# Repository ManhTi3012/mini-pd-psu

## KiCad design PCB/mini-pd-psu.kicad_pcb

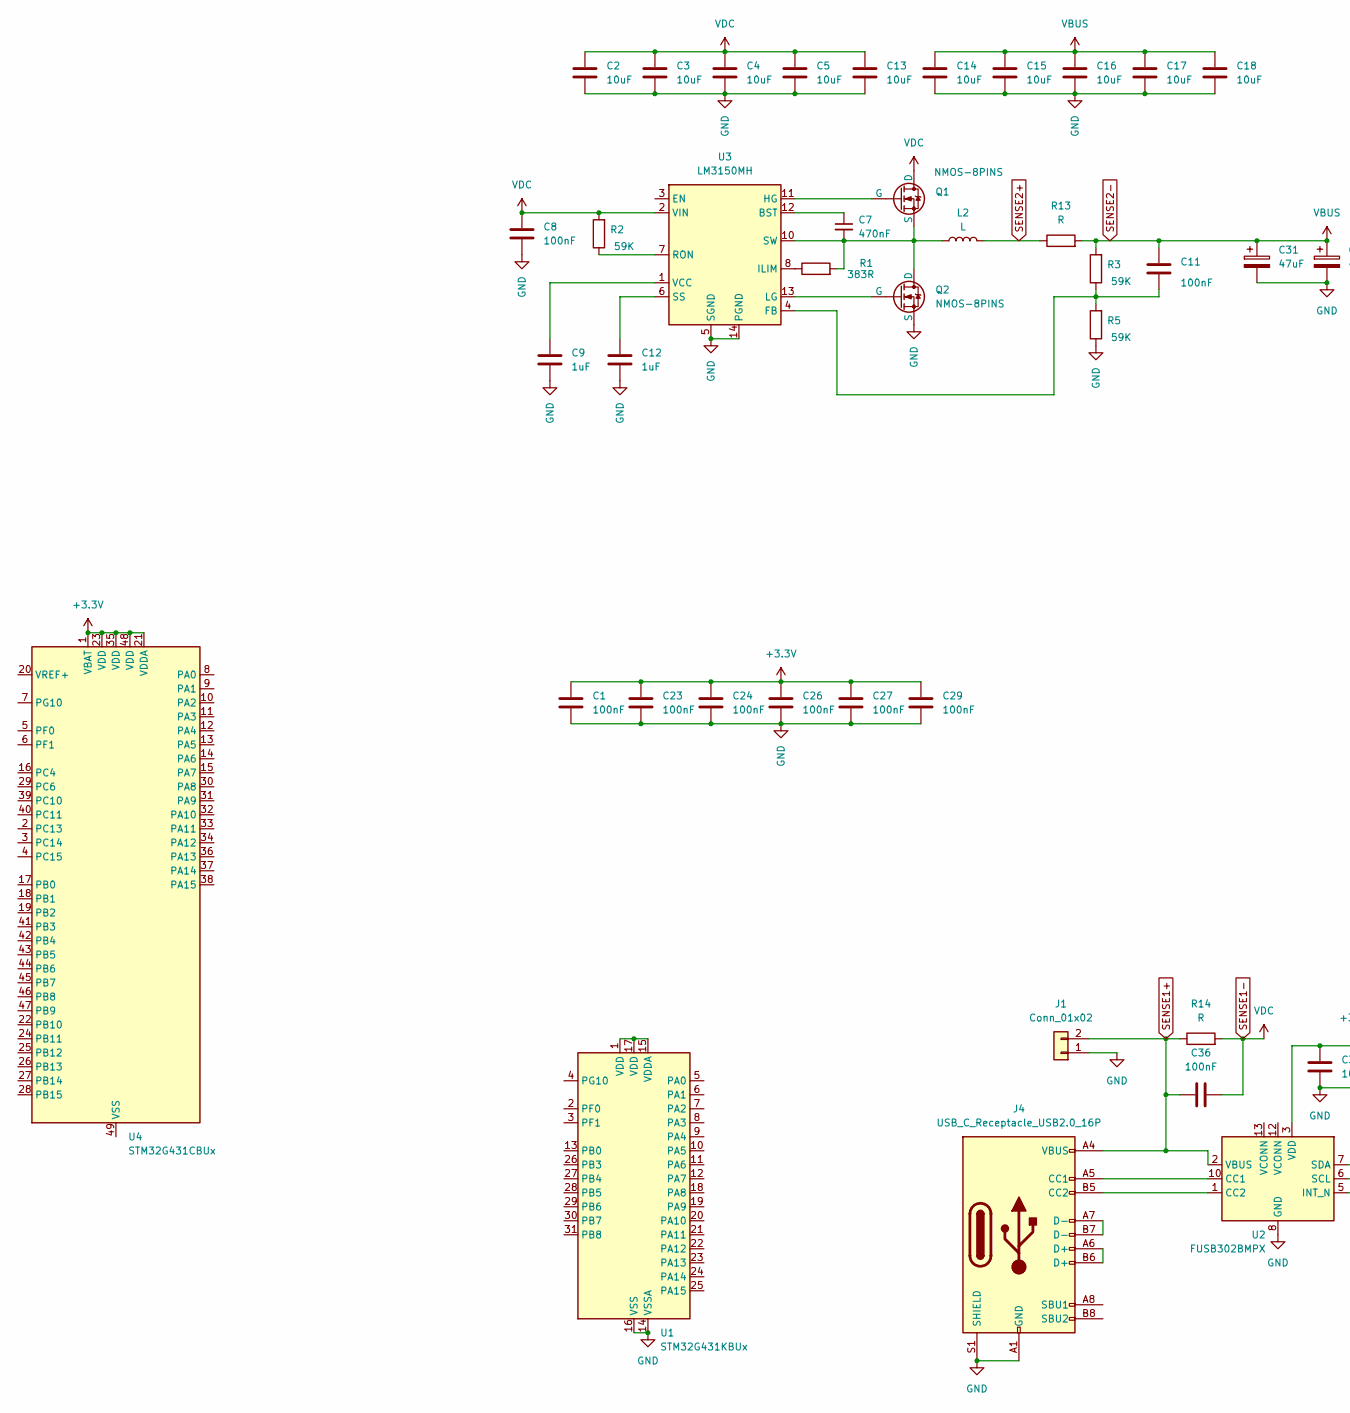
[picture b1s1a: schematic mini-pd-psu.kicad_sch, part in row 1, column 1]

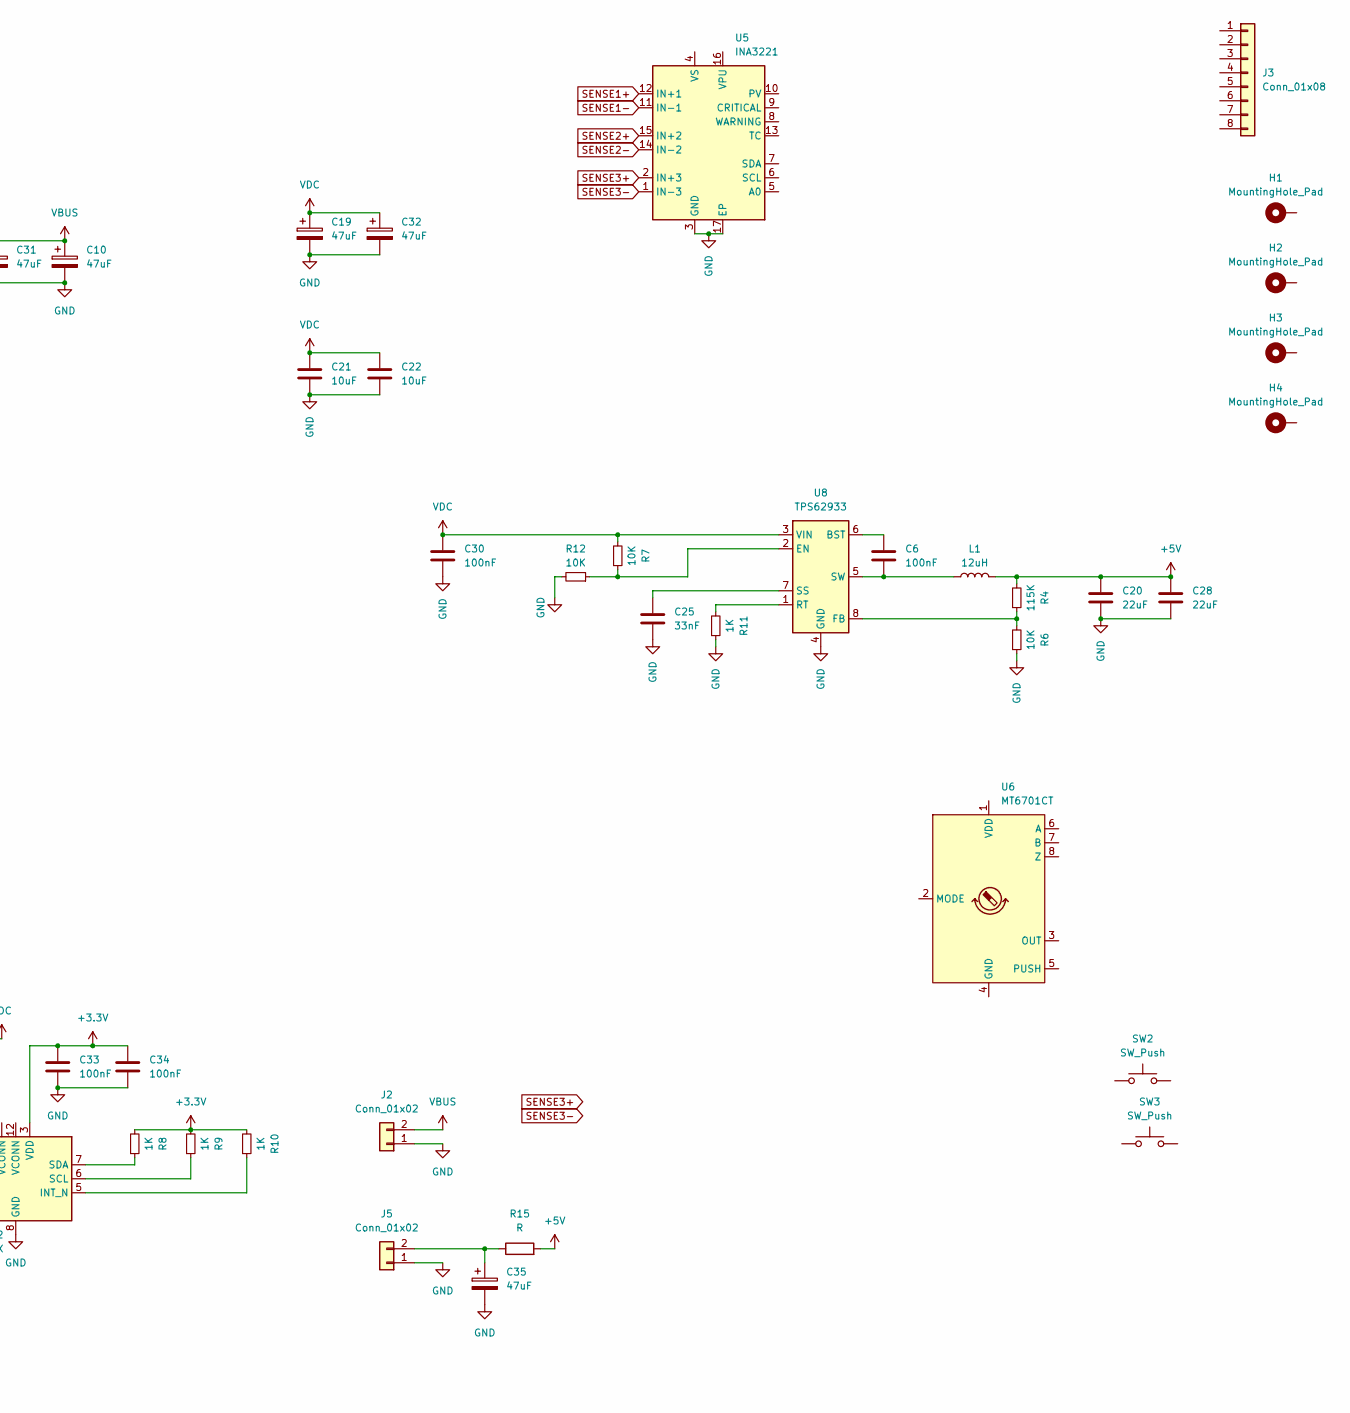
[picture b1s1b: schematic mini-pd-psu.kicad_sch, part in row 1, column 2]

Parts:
C1, C6, C8, C11, C23, C24, C26, C27, C29, C30, C33, C34, C36: 100nF; C_0603_1608Metric
C2, C3, C4, C5, C13, C14, C15, C16, C17, C18, C21, C22: 10uF; C_1206_3216Metric
C7: 470nF; C_0603_1608Metric
C9, C12: 1uF; C_0603_1608Metric
C10, C19, C31, C32, C35: 47uF; CP_Elec_6.3x5.9
C20, C28: 22uF; C_1206_3216Metric
C25: 33nF; C_0603_1608Metric
H1, H2, H3, H4: MountingHole_Pad; MountingHole_2.2mm_M2_Pad_Via
J1: Conn_01x02; AMASS_XT30PW-M_1x02_P2.50mm_Horizontal
J2, J5: Conn_01x02; AMASS_XT30PW-F_1x02_P2.50mm_Horizontal
J3: Conn_01x08
J4: USB_C_Receptacle_USB2.0_16P; USB_C_Receptacle_GCT_USB4105-xx-A_16P_TopMnt_Horizontal
L1: 12uH; L_APV_ANR4020
L2: L; L_7.3x7.3_H4.5
Q1, Q2: NMOS-8PINS; PQFN-8-EP_6x5mm_P1.27mm_Generic
R1: 383R; R_0603_1608Metric
R2, R3, R5: 59K; R_0603_1608Metric
R4: 115K; R_0603_1608Metric
R6, R7, R12: 10K; R_0603_1608Metric
R8, R9, R10, R11: 1K; R_0603_1608Metric
R13, R14, R15: R; R_2512_6332Metric
SW2, SW3: SW_Push
U1: STM32G431KBUx; QFN-32-1EP_5x5mm_P0.5mm_EP3.45x3.45mm
U2: FUSB302BMPX; WQFN-14-1EP_2.5x2.5mm_P0.5mm_EP1.45x1.45mm
U3: LM3150MH; Texas_HTSSOP-14-1EP_4.4x5mm_P0.65mm_EP3.4x5mm_Mask3.155x3.2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
U4: STM32G431CBUx; QFN-48-1EP_7x7mm_P0.5mm_EP5.6x5.6mm
U5: INA3221; Texas_RGV0016A_VQFN-16-1EP_4x4mm_P0.65mm_EP2.1x2.1mm
U6: MT6701CT; SOIC-8_3.9x4.9mm_P1.27mm
U8: TPS62933; SOT-583-8

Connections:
+3.3V: C1.1, C23.1, C24.1, C26.1, C27.1, C29.1, C33.1, C34.1, R8.2, R9.2, R10.2, U2.3 (VDD), U2.4 (VDD), U4.1 (VBAT), U4.21 (VDDA), U4.23 (VDD), U4.35 (VDD), U4.48 (VDD)
+5V: C20.2, C28.2, L1.2, R4.2, R15.2
GND: C1.2, C2.1, C3.1, C4.1, C5.1, C8.2, C9.2, C10.2, C12.2, C13.1, C14.1, C15.1, C16.1, C17.1, C18.1, C19.2, C20.1, C21.1, C22.1, C23.2, C24.2, C25.1, C26.2, C27.2, C28.1, C29.2, C30.1, C31.2, C32.2, C33.2, C34.2, C35.2, J1.1, J2.1, J4.A1 (GND), J4.A12 (GND), J4.B1 (GND), J4.B12 (GND), J4.S1 (SHIELD), J5.1, Q2.1 (S), Q2.2 (S), Q2.3 (S), R5.1, R6.1, R11.1, R12.2, U1.14 (VSSA), U1.16 (VSS), U1.32 (VSS), U1.33 (VSS), U2.8 (GND), U2.9 (GND), U2.15 (GND), U3.5 (SGND), U3.9 (SGND), U3.14 (PGND), U3.15 (SGND), U5.3 (GND), U5.17 (EP), U8.4 (GND)
unnamed: J4.A5 (CC1), U2.10 (CC1), U2.11 (CC1)
unnamed: J4.B5 (CC2), U2.1 (CC2), U2.14 (CC2)
unnamed: J4.A6 (D+), J4.B6 (D+)
unnamed: J4.A7 (D-), J4.B7 (D-)
unnamed: C35.1, J5.2, R15.1
unnamed: Q1.4 (G), U3.11 (HG)
unnamed: C7.2, L2.1, Q1.1 (S), Q1.2 (S), Q1.3 (S), Q2.5 (D), R1.2, U3.10 (SW)
unnamed: Q2.4 (G), U3.13 (LG)
unnamed: U1.1 (VDD), U1.15 (VDDA), U1.17 (VDD)
unnamed: R10.1, U2.5 (INT_N)
unnamed: R9.1, U2.6 (SCL)
unnamed: R8.1, U2.7 (SDA)
unnamed: C7.1, U3.12 (BST)
unnamed: C11.2, R3.1, R5.2, U3.4 (FB)
unnamed: R1.1, U3.8 (ILIM)
unnamed: R2.1, U3.7 (RON)
unnamed: C12.1, U3.6 (SS)
unnamed: C9.1, U3.1 (VCC)
unnamed: C6.2, U8.6 (BST)
unnamed: R7.1, R12.1, U8.2 (EN)
unnamed: R4.1, R6.2, U8.8 (FB)
unnamed: R11.2, U8.1 (RT)
unnamed: C25.2, U8.7 (SS)
unnamed: C6.1, L1.1, U8.5 (SW)
SENSE1+: C36.1, J1.2, J4.A4 (VBUS), J4.A9 (VBUS), J4.B4 (VBUS), J4.B9 (VBUS), R14.1, U2.2 (VBUS), U5.12 (IN+1)
SENSE1-: C2.2, C3.2, C4.2, C5.2, C8.1, C13.2, C19.1, C21.2, C22.2, C30.2, C32.1, C36.2, Q1.5 (D), R2.2, R7.2, R14.2, U3.2 (VIN), U5.11 (IN-1), U8.3 (VIN)
SENSE2+: L2.2, R13.1, U5.15 (IN+2)
SENSE2-: C10.1, C11.1, C14.2, C15.2, C16.2, C17.2, C18.2, C31.1, J2.2, R3.2, R13.2, U5.14 (IN-2)
SENSE3+: U5.2 (IN+3)
SENSE3-: U5.1 (IN-3)

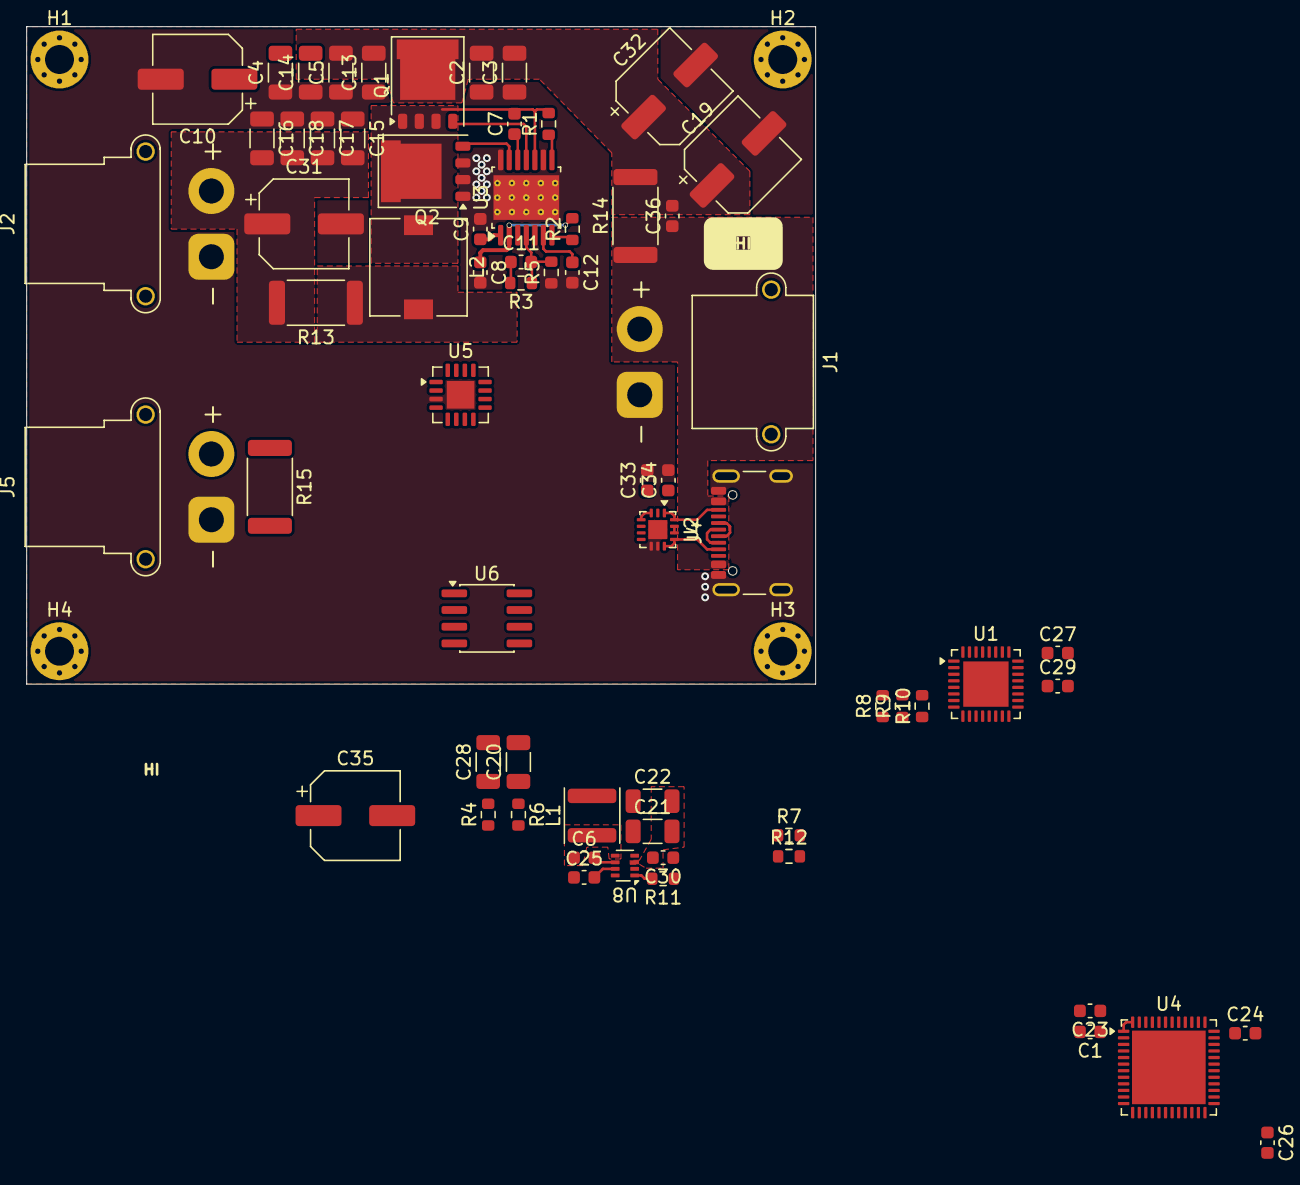
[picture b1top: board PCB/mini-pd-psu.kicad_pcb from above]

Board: 2 copper layers, 60.0 x 50.0 mm, 70 parts (0 on the bottom side), 31 nets.

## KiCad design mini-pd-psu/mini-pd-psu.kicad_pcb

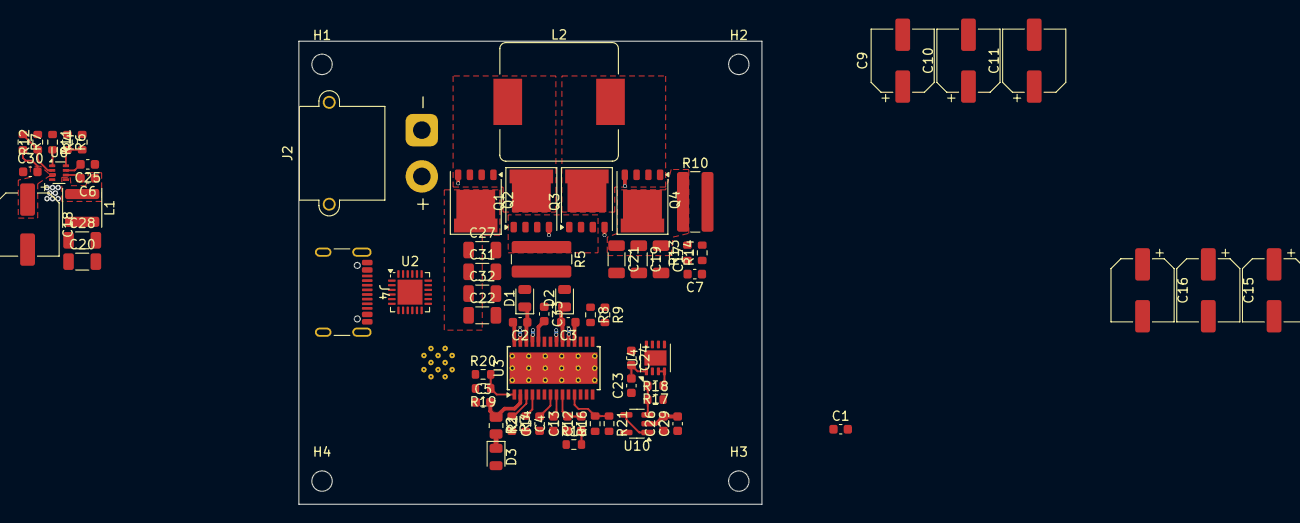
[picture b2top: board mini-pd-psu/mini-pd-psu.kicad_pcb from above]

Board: 4 copper layers, 50.0 x 50.0 mm, 75 parts (1 on the bottom side), 41 nets.

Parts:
C1: C; C_0603_1608Metric
C2, C3, C4, C5, C6, C12, C13, C14, C24, C26, C30, C33: 100nF; C_0603_1608Metric
C7, C23, C29: 1uF; C_0603_1608Metric
C8, C9, C10, C11, C15, C16: C_Polarized; CP_Elec_6.3x5.9
C17, C19, C21, C22, C27, C31, C32: 10uF; C_1206_3216Metric
C18: 47uF; CP_Elec_6.3x7.7
C20, C28: 22uF; C_1206_3216Metric
C25: 33nF; C_0603_1608Metric
D1, D2, D3: D_Schottky; D_0805_2012Metric
H1, H2, H3, H4: MountingHole; MountingHole_2.2mm_M2
J2: Conn_01x02; AMASS_XT30PW-M_1x02_P2.50mm_Horizontal
J4: USB_C_Receptacle_USB2.0_16P; USB_C_Receptacle_GCT_USB4105-xx-A_16P_TopMnt_Horizontal
L1: 12uH; L_APV_ANR4020
L2: 4.7uH; L_TaiTech_TMPC1265_13.5x12.5mm
Q1, Q2, Q3, Q4: AON6264E; PQFN-8-EP_6x5mm_P1.27mm_Generic
R1, R19, R20: 93.1K; R_0603_1608Metric
R2: 10R; R_0805_2012Metric
R3, R15: 2K; R_0603_1608Metric
R4: 115K; R_0603_1608Metric
R5, R10: 8mR; R_1225_3264Metric
R6, R7, R12: 10K; R_0603_1608Metric
R8, R9, R13, R14, R17, R18: 100R; R_0603_1608Metric
R11: 1K; R_0603_1608Metric
R16, R21: 100K; R_0603_1608Metric
U1: ESP32-WROOM-32
U2: STUSB4500QTR; QFN-24-1EP_4x4mm_P0.5mm_EP2.7x2.7mm
U3: LM5176PWP; HTSSOP-28-1EP_4.4x9.7mm_P0.65mm_EP3.4x9.5mm_ThermalVias
U4: DAC8560IxDGK; VSON-8-1EP_3x3mm_P0.65mm_EP1.65x2.4mm
U8: TPS62933; SOT-583-8
U10: OPA376xxDBV; SOT-23-5

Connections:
+3.3V: C23.2, C24.2, C26.2, C29.2, U1.2 (VDD), U4.1 (V_{DD}), U10.2 (V-)
+10V: C20.2, C28.2, L1.2, R4.2
BIAS: C8.1, C15.1, C16.1, C33.2, R10.2, R14.2, R16.1, U3.12 (VOSNS), U3.24 (BIAS)
CS: R8.2, U3.16 (CS)
CSG: R9.2, U3.15 (CSG)
FB: R16.2, R21.1, U3.11 (FB)
GND: C4.1, C5.1, C8.2, C9.2, C10.2, C11.2, C13.1, C14.1, C15.2, C16.2, C17.2, C18.2, C19.2, C20.1, C21.2, C22.2, C23.1, C24.1, C25.1, C26.1, C27.2, C28.1, C29.1, C30.1, C31.2, C32.2, C33.1, J2.1, J4.A1 (GND), J4.A12 (GND), J4.B1 (GND), J4.B12 (GND), R1.1, R5.2, R6.1, R9.1, R11.1, R12.2, R15.1, R18.2, R20.1, U1.1 (GND), U1.15 (GND), U1.38 (GND), U1.39 (GND), U2.10 (GND), U2.25 (GND), U3.5 (DITH), U3.10 (AGND), U3.22 (PGND), U3.29 (PowerPAD), U4.8 (GND), U8.4 (GND), U10.5 (V+)
HDRV1: Q2.4 (G), U3.27 (HDRV1)
HDRV2: Q4.4 (G), U3.19 (HDRV2)
ISNS+: C7.2, R13.1, U3.14 (ISNS(+))
ISNS-: C7.1, R14.1, U3.13 (ISNS(-))
LDRV1: Q1.4 (G), U3.25 (LDRV1)
LDRV2: Q3.4 (G), U3.21 (LDRV2)
unnamed: C12.1, R15.2
unnamed: C17.1, C19.1, C21.1, Q4.5 (D), R10.1, R13.2
unnamed: C2.1, D1.1 (K), U3.26 (BOOT1)
unnamed: C3.2, D2.1 (K), U3.20 (BOOT2)
unnamed: D3.1 (K), R2.2
unnamed: J4.A6 (D+), J4.B6 (D+)
unnamed: J4.A7 (D-), J4.B7 (D-)
unnamed: Q1.1 (S), Q1.2 (S), Q1.3 (S), Q3.1 (S), Q3.2 (S), Q3.3 (S), R5.1, R8.1
unnamed: C12.2, C13.2, U3.9 (COMP)
unnamed: R1.2, U3.4 (MODE)
unnamed: C14.2, U3.7 (SLOPE)
unnamed: C4.2, U3.8 (SS)
unnamed: C2.2, L2.1, Q1.5 (D), Q2.1 (S), Q2.2 (S), Q2.3 (S), U3.28 (SW1)
unnamed: C3.1, L2.2, Q3.5 (D), Q4.1 (S), Q4.2 (S), Q4.3 (S), U3.18 (SW2)
unnamed: C5.2, R2.1, U3.2 (VIN)
unnamed: R3.1, U3.3 (VISNS)
unnamed: R17.1, U4.3 (V_{FB}), U4.4 (V_{OUT})
unnamed: C6.2, U8.6 (BST)
unnamed: R7.1, R12.1, U8.2 (EN)
unnamed: R4.1, R6.2, U8.8 (FB)
unnamed: R11.2, U8.1 (RT)
unnamed: C25.2, U8.7 (SS)
unnamed: C6.1, L1.1, U8.5 (SW)
unnamed: R17.2, R18.1, U10.3 (+)
unnamed: R21.2, U10.1, U10.4 (-)
POWER_EN: R19.1, R20.2, U3.1 (EN/UVLO)
VCC: D1.2 (A), D2.2 (A), U3.23 (VCC)
VDC: C9.1, C10.1, C11.1, C18.1, C22.1, C27.1, C30.2, C31.1, C32.1, D3.2 (A), J2.2, J4.A4 (VBUS), J4.A9 (VBUS), J4.B4 (VBUS), J4.B9 (VBUS), Q2.5 (D), R3.2, R7.2, R19.2, U8.3 (VIN)

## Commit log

2025-12-27 update
    change to buck only and smaller footprint
    change to stm32
